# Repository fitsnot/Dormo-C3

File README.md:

# Dormo

The Dormo is a tiny IoT device with extremely long battery life and snappy response time, making it ideal for a multi-button smart home remote.
This project started as a fork of [Picoclick-C3](https://github.com/makermoekoe/Picoclick-C3) which focuses on overall size and offers limited expandability.

## Current State

The short term goal is to have a ready-to order PCB at JLCPCB with the respective parts for assembly. If you have suggestions simply open a feature request issue.

- [x] Update schematic in KiCad
- [x] Draw PCB
- [ ] Validate prototype PCB
- [ ] Design 3D-printable housing

Images of the first housing design:

</a>
</a>

## GPIOs

Function | GPIO C3T | GPIO C3 | Mode
-------- | -------- | -------- | --------
LED | GPIO6 | GPIO6 (CLK) + GPIO7 (SDI) | Output
Latch* | GPIO3 | ** | Output
Button | GPIO5 | GPIO5 | Input
Charge Stat. | GPIO1  | ext. LED | Input
Bat Voltage | GPIO4 | GPIO4 | Input
Bat Voltage EN | -- | GPIO3 | Output

*Enabling the LDO can be done by pressing the button of the device or turning the latch high. In most use cases, the latch GPIO should be turned on as the first task of the Picoclick. Once the task is completed the device can be powered off by turning the latch off (e.g. pulling it low).

**The Picoclick C3 doesn't need a latching GPIO because it uses the embedded flash's power supply pin as a reference. It can be depowered with putting the ESP32 in deepsleep. To reduce the power consumption of the ESP32 this function will disable the power of the embedded flash (`VDD_SPI`) which in result will depower the Picoclick itself. The deepsleep calling function is only necessary to pulling the `VDD_SPI` line low, not to use the deepsleep mode of the ESP32.

## Reducing power consumption

In order to reduce the power consumption of the Picoclick the following points can be done:

- Disable WiFi while not in use (e.g. if using LED animations only): `WiFi.mode(WIFI_OFF);`
- Reducing CPU frequency after WiFi stuff is completed (crystal is 40MHz): `setCpuFrequencyMhz(10); //reduce to 10MHz`
- Reducing brightness of the LEDs (can be done right after FastLED init): `FastLED.setBrightness(150);`

## Flashing firmware to the ESP32 (C3T)

**- Press and hold the button during the complete flashing process! Otherwise the ESP32 will be loose power and the upload process will crash!**

**- A battery or a power supply has to be applied to the battery pads (3.5v - 5.5v) in order to flash the device!**

Except the above, the Picoclick behaves like a normal development board. No need to get the ESP32 into download mode or pressing any reset button.

## Speed up boot process

Things makermoekoe has done so far:
- Set *Flash SPI mode* from *DIO* to *QIO* (in Serial flasher config)
- Set *Log output* from *Info* to *Warning* (in component config)
- Set *Bootloader log verbosity* from *Info* to *Warning* (in Bootloader config)
- Enable *Skip image validation from power on* (in Bootloader config)

These points result in a boot up time of around 68ms which is almost quite fantastic. The test I've done so far were quite sufficient. If it is possible to make it even faster or if you have other ideas which could lead into the right direction then please let me know!

## Battery for the Picoclick

** TODO **

As the Picoclick C3 comes with an embedded battery protection, the protection of the LiPo battery itself is redundant. Therefore you can use these tiny cells which are used by BT headsets. They come in a 401010 or 301010 package.

## Cases for the C3T

** TODO **

# FAQ

[Main documentation of the Picoclick-C3 can be found here!](https://makermoekoe.gitbook.io/picoclick-c3/)

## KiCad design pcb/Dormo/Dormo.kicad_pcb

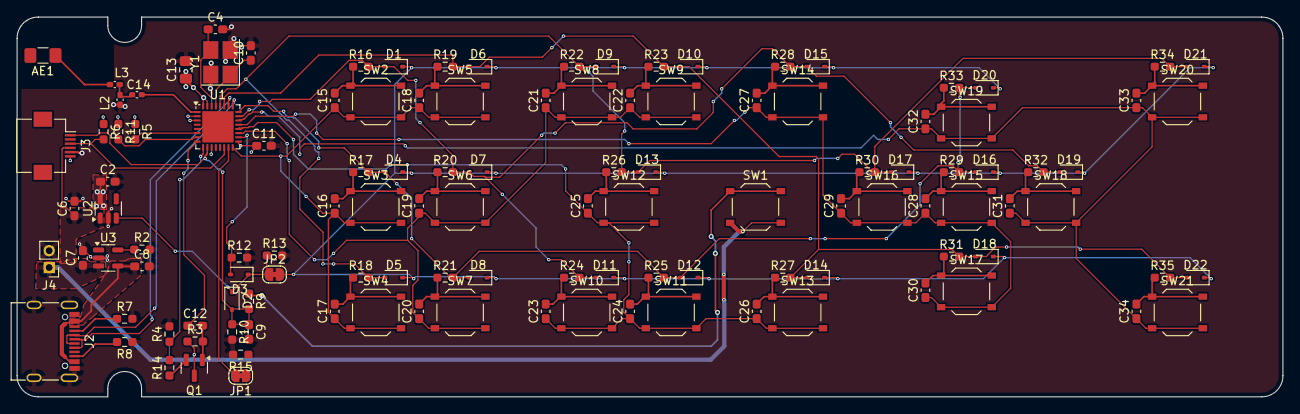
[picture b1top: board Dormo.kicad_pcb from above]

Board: 4 copper layers, 150.0 x 45.0 mm, 121 parts (0 on the bottom side), 57 nets.

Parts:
AE1: 2.4GHz chip ant; L_1206_3216Metric_Pad1.42x1.75mm_HandSolder
C2, C6, C7, C8, C9: 1uF; C_0603_1608Metric_Pad1.08x0.95mm_HandSolder
C4, C10: 20pF; C_0603_1608Metric_Pad1.08x0.95mm_HandSolder
C11, C12: 100nF; C_0603_1608Metric_Pad1.08x0.95mm_HandSolder
C13: 10uF; C_0805_2012Metric_Pad1.18x1.45mm_HandSolder
C14: 1.2pF; C_0402_1005Metric_Pad0.74x0.62mm_HandSolder
C15, C16, C17, C18, C19, C20, C21, C22, C23, C24, C25, C26, C27, C28, C29, C30, C31, C32, C33, C34: 1nF; C_0603_1608Metric_Pad1.08x0.95mm_HandSolder
D1, D4, D5, D6, D7, D8, D9, D10, D11, D12, D13, D14, D15, D16, D17, D18, D19, D20, D21, D22: 1N5819WS; D_SOD-323
D2, D3: 1N4148WS; D_SOD-323
J2: USB_C_Receptacle_USB2.0_16P; USB_C_Receptacle_G-Switch_GT-USB-7010ASV
J3: FPC, 6P, P=0.5mm; Hirose_FH12-6S-0.5SH_1x06-1MP_P0.50mm_Horizontal
J4: Conn_01x02; PinHeader_1x02_P2.00mm_Vertical
JP1, JP2: Bridged; SolderJumper-2_P1.3mm_Bridged_RoundedPad1.0x1.5mm
L2: 2.7nH; L_0402_1005Metric_Pad0.77x0.64mm_HandSolder
L3: 3.3nH; L_0402_1005Metric_Pad0.77x0.64mm_HandSolder
Q1: AO3401A; SOT-23
R2: 47k; R_0603_1608Metric_Pad0.98x0.95mm_HandSolder
R3, R12: 1M; R_0603_1608Metric_Pad0.98x0.95mm_HandSolder
R4, R14: 100k; R_0603_1608Metric_Pad0.98x0.95mm_HandSolder
R5, R6, R10, R11, R13, R15: 10k; R_0603_1608Metric_Pad0.98x0.95mm_HandSolder
R7, R8: 5k1; R_0603_1608Metric_Pad0.98x0.95mm_HandSolder
R9: 1k; R_0603_1608Metric_Pad0.98x0.95mm_HandSolder
R16, R17, R18, R19, R20, R21, R22, R23, R24, R25, R26, R27, R28, R29, R30, R31, R32, R33, R34, R35: 470R; R_0603_1608Metric_Pad0.98x0.95mm_HandSolder
SW1, SW2, SW3, SW4, SW5, SW6, SW7, SW8, SW9, SW10, SW11, SW12, SW13, SW14, SW15, SW16, SW17, SW18, SW19, SW20, SW21: SW_Push_1P1T_XKB_TS-1187A
U1: ESP32-C3; QFN-32-1EP_5x5mm_P0.5mm_EP3.7x3.7mm
U2: MIC5504-3.3YM5; SOT-23-5
U3: BRCL4054BME; SOT-23-5
Y1: 40MHz; Crystal_SMD_3225-4Pin_3.2x2.5mm_HandSoldering

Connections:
/+3V3: C2.1, C11.1, C13.1, J3.6, R5.1, R6.1, R11.1, U1.2 (VDD3P3), U1.3 (VDD3P3), U1.11 (VDD3P3_RTC), U1.17 (VDD3P3_CPU), U1.31 (VDDA), U1.32 (VDDA), U2.5 (VOUT)
/+VBAT: C6.1, C7.1, J3.4, J4.1, Q1.3 (D), R3.1, SW1.2, U2.1 (VIN), U3.3 (BAT)
/+VSENSE: R4.1, R14.2, U1.9 (MTMS)
/+VUSB: C8.1, J2.A4 (VBUS), J2.A9 (VBUS), J2.B4 (VBUS), J2.B9 (VBUS), U3.4 (VCC)
/BTN: C9.1, D2.2 (A), J3.1, R9.2, R10.1, U1.10 (MTDI)
/COL_1: D1.2 (A), D7.2 (A), D11.2 (A), D15.2 (A), D19.2 (A), R16.2, R20.2, R24.2, R28.2, R32.2, U1.23 (SPID)
/COL_2: D4.2 (A), D8.2 (A), D12.2 (A), D16.2 (A), D20.2 (A), R17.2, R21.2, R25.2, R29.2, R33.2, U1.24 (SPIQ)
/COL_3: D5.2 (A), D9.2 (A), D13.2 (A), D17.2 (A), D21.2 (A), R18.2, R22.2, R26.2, R30.2, R34.2, U1.28 (U0TXD)
/COL_4: D6.2 (A), D10.2 (A), D14.2 (A), D18.2 (A), D22.2 (A), R19.2, R23.2, R27.2, R31.2, R35.2, U1.27 (U0RXD)
/EN: R11.2, U1.7 (CHIP_EN)
/EN_LDO: D2.1 (K), D3.1 (K), JP2.1 (A), R13.1, U2.3 (EN)
/EN_VSENSE: C12.1, U1.8 (GPIO3)
/GPIO02: J3.2, R5.2, U1.6 (GPIO2)
/GPIO08: J3.3, R6.2, U1.14 (GPIO8)
/GPIO09: JP1.2 (B), U1.15 (GPIO9)
/GPIO10: C15.1, C16.1, C17.1, C18.1, SW2.2, SW3.2, SW4.2, SW5.2, U1.16 (GPIO10)
/GPIO11: D3.2 (A), R12.1, U1.18 (VDD_SPI)
/GPIO12: C19.1, C20.1, C21.1, C22.1, SW6.2, SW7.2, SW8.2, SW9.2, U1.19 (SPIHD)
/GPIO13: C23.1, C24.1, C25.1, C26.1, SW10.2, SW11.2, SW12.2, SW13.2, U1.20 (SPIWP)
/GPIO14: C27.1, C28.1, C29.1, C30.1, SW14.2, SW15.2, SW16.2, SW17.2, U1.21 (SPICS0)
/GPIO15: C31.1, C32.1, C33.1, C34.1, SW18.2, SW19.2, SW20.2, SW21.2, U1.22 (SPICLK)
/GPIO18: J2.A7 (D-), J2.B7 (D-), U1.25 (GPIO18)
/GPIO19: J2.A6 (D+), J2.B6 (D+), U1.26 (GPIO19)
/LATCH_MX: D1.1 (K), D4.1 (K), D5.1 (K), D6.1 (K), D7.1 (K), D8.1 (K), D9.1 (K), D10.1 (K), D11.1 (K), D12.1 (K), D13.1 (K), D14.1 (K), D15.1 (K), D16.1 (K), D17.1 (K), D18.1 (K), D19.1 (K), D20.1 (K), D21.1 (K), D22.1 (K), JP2.2 (B)
GND: AE1.2 (PCB_Trace), C2.2, C4.2, C6.2, C7.2, C8.2, C9.2, C10.2, C11.2, C13.2, J2.A1 (GND), J2.A12 (GND), J2.B1 (GND), J2.B12 (GND), J2.S1 (SHIELD), J3.5, J4.2, L2.2, R2.2, R4.2, R7.2, R8.1, R10.2, R12.2, R13.2, R15.2, U1.33 (GND), U2.2 (GND), U3.2 (GND), Y1.2, Y1.4
unnamed: AE1.1 (FEED), L3.2
unnamed: C14.2, L2.1, L3.1
unnamed: C15.2, R16.1, SW2.1
unnamed: C16.2, R17.1, SW3.1
unnamed: C17.2, R18.1, SW4.1
unnamed: C18.2, R19.1, SW5.1
unnamed: C19.2, R20.1, SW6.1
unnamed: C20.2, R21.1, SW7.1
unnamed: C21.2, R22.1, SW8.1
unnamed: C22.2, R23.1, SW9.1
unnamed: C23.2, R24.1, SW10.1
unnamed: C24.2, R25.1, SW11.1
unnamed: C25.2, R26.1, SW12.1
unnamed: C26.2, R27.1, SW13.1
unnamed: C27.2, R28.1, SW14.1
unnamed: C28.2, R29.1, SW15.1
unnamed: C29.2, R30.1, SW16.1
unnamed: C30.2, R31.1, SW17.1
unnamed: C31.2, R32.1, SW18.1
unnamed: C32.2, R33.1, SW19.1
unnamed: C33.2, R34.1, SW20.1
unnamed: C34.2, R35.1, SW21.1
unnamed: J2.A5 (CC1), R7.1
unnamed: J2.B5 (CC2), R8.2
unnamed: JP1.1 (A), R15.1
unnamed: C12.2, Q1.1 (G), R3.2
unnamed: Q1.2 (S), R14.1
unnamed: R9.1, SW1.1
unnamed: C14.1, U1.1 (LNA_IN)
unnamed: C10.1, U1.29 (XTAL_N), Y1.1
unnamed: C4.1, U1.30 (XTAL_P), Y1.3
unnamed: R2.1, U3.5 (PROG)

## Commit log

2025-05-04 rough first schematic draft
2025-05-05 cleanup schematic
2025-05-06 added button matrix in schematic
2025-05-08 first pcb components layout
2025-05-13 minor layout tweaks
2025-05-14 first pass of PCB routing
2025-05-26 minor adjustements
2025-06-01 first draft of housing design
